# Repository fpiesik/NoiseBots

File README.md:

# NoiseBots
 A modular music making robot design

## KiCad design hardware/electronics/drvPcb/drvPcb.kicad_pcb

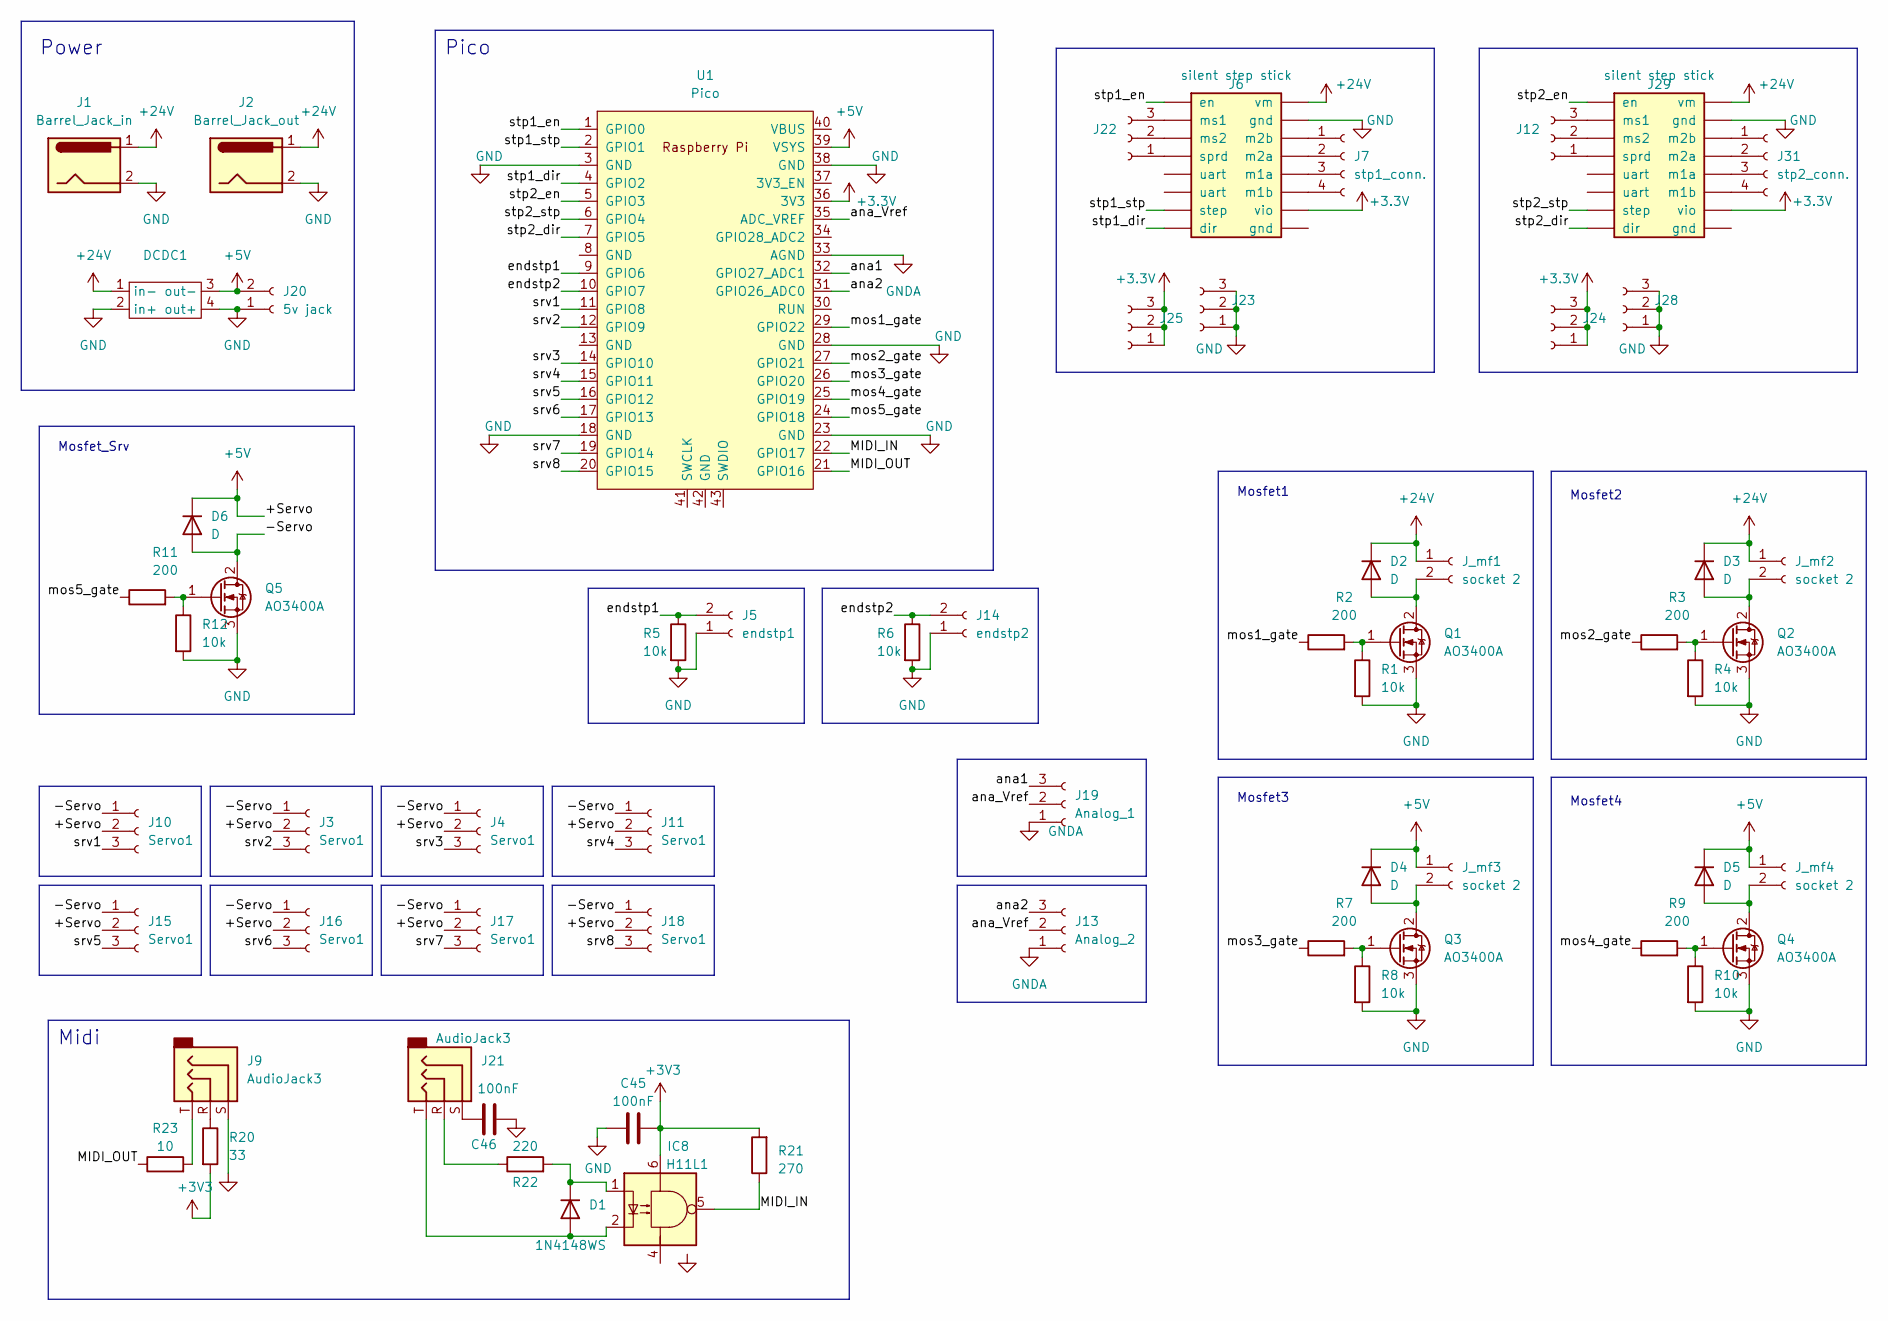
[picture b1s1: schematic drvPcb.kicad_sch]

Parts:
C45, C46: 100nF; C_1206_3216Metric_Pad1.33x1.80mm_HandSolder; LCSC C14663
D1: 1N4148WS; D_1206_3216Metric_Pad1.42x1.75mm_HandSolder; LCSC C2128
D2, D3, D4, D5, D6: D; D_1206_3216Metric_Pad1.42x1.75mm_HandSolder
DCDC1: Converter_DCDC
IC8: H11L1; SMDIP-6_W9.53mm; LCSC C78589
J1: Barrel_Jack_in; BarrelJack_GCT_DCJ200-10-A_Horizontal(fmod)
J2: Barrel_Jack_out; BarrelJack_GCT_DCJ200-10-A_Horizontal(fmod)
J3, J4, J10, J11, J15, J16, J17, J18: Servo1; PinHeader_1x03_P2.54mm_Vertical(fmod)
J5: endstp1; PinHeader_1x02_P2.54mm_Vertical_(fmod)
J6, J29: silent step stick; stepstick
J7: stp1_conn.; PinHeader_1x04_P2.54mm_Vertical(fmod)
J9, J21: AudioJack3; Jack_3.5mm_CUI_SJ1-3523N_Horizontal(fmod)
J12, J22, J23, J24, J25, J28: Conn_01x03_Socket; PinHeader_1x03_P2.54mm_Vertical(fmod)
J13: Analog_2; PinHeader_1x03_P2.54mm_Vertical(fmod)
J14: endstp2; PinHeader_1x02_P2.54mm_Vertical_(fmod)
J19: Analog_1; PinHeader_1x03_P2.54mm_Vertical(fmod)
J20: 5v jack; PinHeader_1x02_P2.54mm_Vertical_(fmod)
J31: stp2_conn.; PinHeader_1x04_P2.54mm_Vertical(fmod)
J_mf1, J_mf2, J_mf3, J_mf4: socket 2; PinHeader_1x02_P2.54mm_Vertical_(fmod)
Q1, Q2, Q3, Q4, Q5: AO3400A; SOT-223-3_TabPin2
R1, R4, R5, R6, R8, R10, R12: 10k; R_1206_3216Metric_Pad1.30x1.75mm_HandSolder
R2, R3, R7, R9, R11: 200; R_1206_3216Metric_Pad1.30x1.75mm_HandSolder
R20: 33; R_1206_3216Metric_Pad1.30x1.75mm_HandSolder; LCSC C23140
R21: 270; R_1206_3216Metric_Pad1.30x1.75mm_HandSolder; LCSC C22966
R22: 220; R_1206_3216Metric_Pad1.30x1.75mm_HandSolder; LCSC C25905
R23: 10; R_1206_3216Metric_Pad1.30x1.75mm_HandSolder; LCSC C22859
U1: Pico; RPi_Pico_SMD_TH

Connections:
+3.3V: J6.10 (vio), J24.1, J24.2, J24.3, J25.1, J25.2, J25.3, J29.10 (vio), U1.36 (3V3)
+3V3: C45.2, IC8.6, R20.2, R21.2
+5V: D4.1 (K), D5.1 (K), D6.1 (K), DCDC1.3 (out-), J3.2, J4.2, J10.2, J11.2, J15.2, J16.2, J17.2, J18.2, J20.2, J_mf3.1, J_mf4.1, U1.39 (VSYS)
+24V: D2.1 (K), D3.1 (K), DCDC1.1 (in-), J1.1, J2.1, J6.16 (vm), J29.16 (vm), J_mf1.1, J_mf2.1
/-Servo: D6.2 (A), J3.1, J4.1, J10.1, J11.1, J15.1, J16.1, J17.1, J18.1, Q5.2 (D)
/MIDI_IN: IC8.5, R21.1, U1.22 (GPIO17)
/MIDI_OUT: R23.1, U1.21 (GPIO16)
/ana1: J19.3, U1.32 (GPIO27_ADC1)
/ana2: J13.3, U1.31 (GPIO26_ADC0)
/ana_Vref: J13.2, J19.2, U1.35 (ADC_VREF)
/endstp1: J5.2, R5.1, U1.9 (GPIO6)
/endstp2: J14.2, R6.1, U1.10 (GPIO7)
/mos1_gate: R2.1, U1.29 (GPIO22)
/mos2_gate: R3.1, U1.27 (GPIO21)
/mos3_gate: R7.1, U1.26 (GPIO20)
/mos4_gate: R9.1, U1.25 (GPIO19)
/mos5_gate: R11.1, U1.24 (GPIO18)
/srv1: J10.3, U1.11 (GPIO8)
/srv2: J3.3, U1.12 (GPIO9)
/srv3: J4.3, U1.14 (GPIO10)
/srv4: J11.3, U1.15 (GPIO11)
/srv5: J15.3, U1.16 (GPIO12)
/srv6: J16.3, U1.17 (GPIO13)
/srv7: J17.3, U1.19 (GPIO14)
/srv8: J18.3, U1.20 (GPIO15)
/stp1_dir: J6.8 (dir), U1.4 (GPIO2)
/stp1_en: J6.1 (en), U1.1 (GPIO0)
/stp1_stp: J6.7 (step), U1.2 (GPIO1)
/stp2_dir: J29.8 (dir), U1.7 (GPIO5)
/stp2_en: J29.1 (en), U1.5 (GPIO3)
/stp2_stp: J29.7 (step), U1.6 (GPIO4)
GND: C45.1, C46.2, DCDC1.2 (in+), DCDC1.4 (out+), J1.2, J2.2, J5.1, J6.15 (gnd), J9.S, J14.1, J20.1, J23.1, J23.2, J23.3, J28.1, J28.2, J28.3, J29.15 (gnd), Q1.3 (S), Q2.3 (S), Q3.3 (S), Q4.3, Q5.3 (S), R1.2, R4.2, R5.2, R6.2, R8.2, R10.2, R12.2, U1.3 (GND), U1.18 (GND), U1.23 (GND), U1.28 (GND), U1.38 (GND)
GNDA: J13.1, J19.1, U1.33 (AGND)
unnamed: C46.1, J21.S
unnamed: D1.2 (A), IC8.2, J21.T
unnamed: D1.1 (K), IC8.1, R22.2
unnamed: D2.2 (A), J_mf1.2, Q1.2 (D)
unnamed: D3.2 (A), J_mf2.2, Q2.2 (D)
unnamed: D4.2 (A), J_mf3.2, Q3.2 (D)
unnamed: D5.2 (A), J_mf4.2, Q4.2
unnamed: J6.12 (m1a), J7.3
unnamed: J6.11 (m1b), J7.4
unnamed: J6.13 (m2a), J7.2
unnamed: J6.14 (m2b), J7.1
unnamed: J9.R, R20.1
unnamed: J9.T, R23.2
unnamed: J12.1, J29.4 (sprd)
unnamed: J12.2, J29.3 (ms2)
unnamed: J12.3, J29.2 (ms1)
unnamed: J21.R, R22.1
unnamed: J6.4 (sprd), J22.1
unnamed: J6.3 (ms2), J22.2
unnamed: J6.2 (ms1), J22.3
unnamed: J29.12 (m1a), J31.3
unnamed: J29.11 (m1b), J31.4
unnamed: J29.13 (m2a), J31.2
unnamed: J29.14 (m2b), J31.1
unnamed: Q1.1 (G), R1.1, R2.2
unnamed: Q2.1 (G), R3.2, R4.1
unnamed: Q3.1 (G), R7.2, R8.1
unnamed: Q4.1 (G), R9.2, R10.1
unnamed: Q5.1 (G), R11.2, R12.1

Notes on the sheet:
Midi
Mosfet3
Mosfet1
Mosfet2
Pico
Mosfet4
Power
Mosfet_Srv

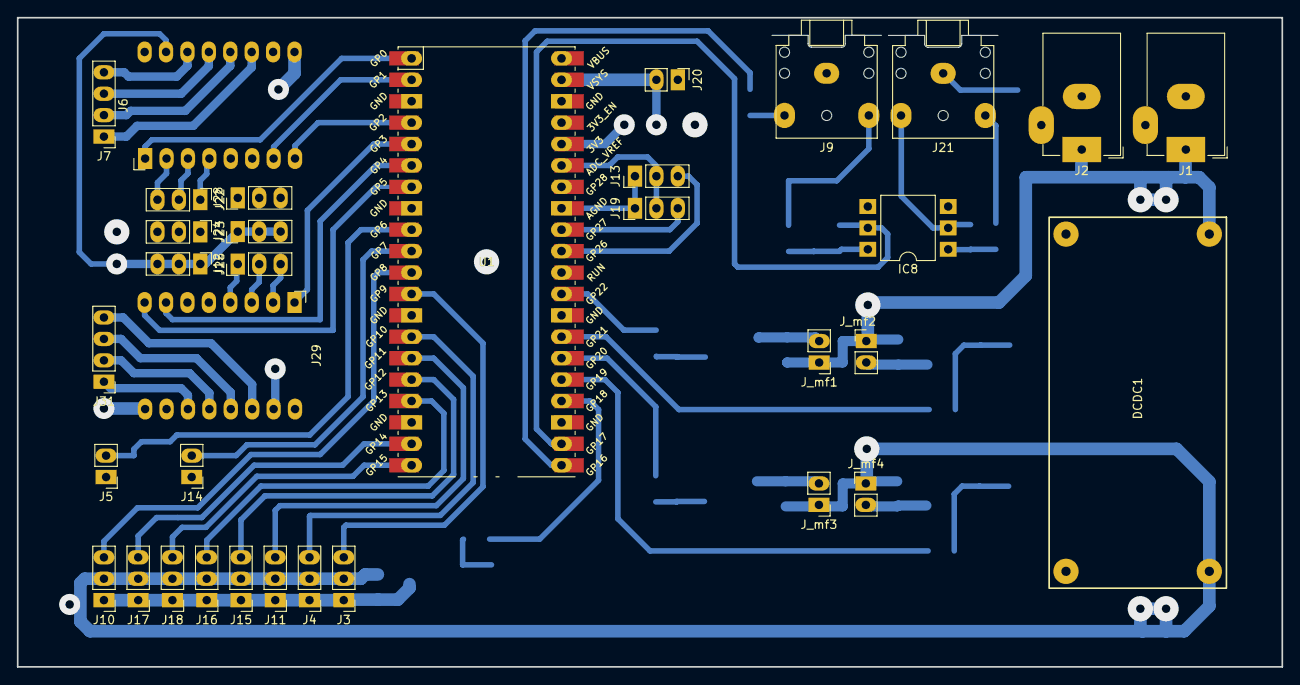
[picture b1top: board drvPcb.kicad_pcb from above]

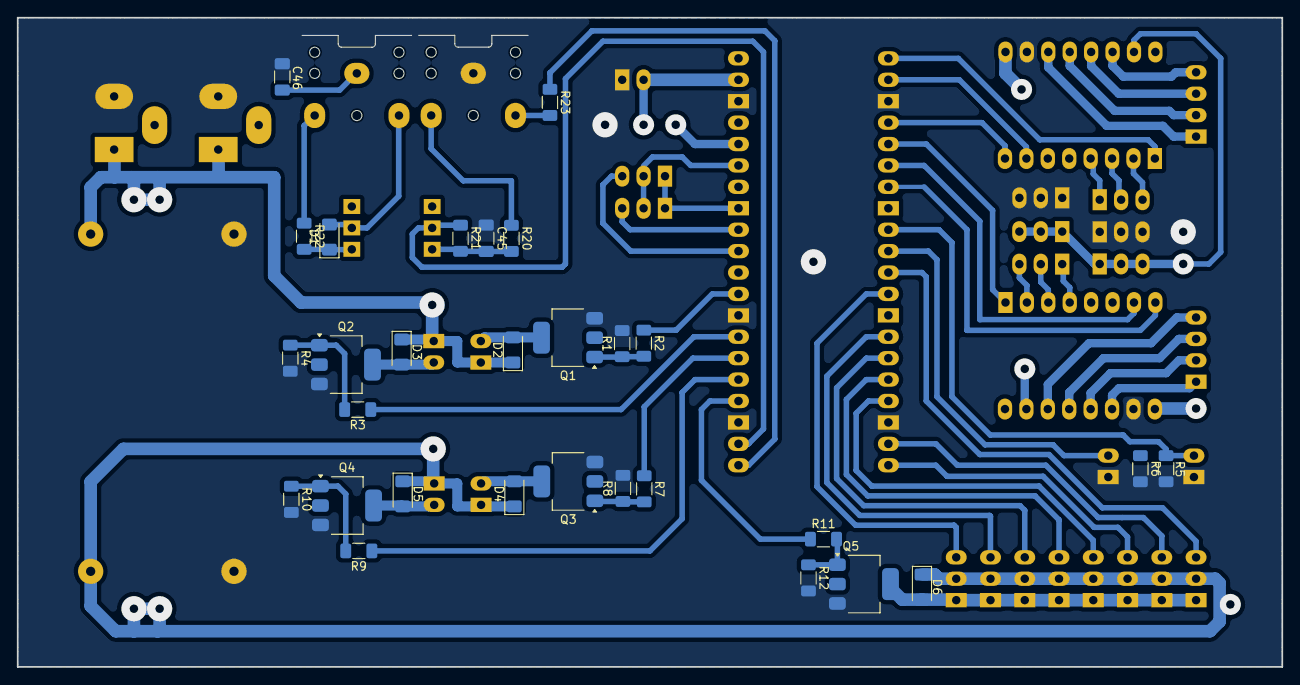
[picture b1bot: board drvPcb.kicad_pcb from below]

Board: 2 copper layers, 150.0 x 77.0 mm, 63 parts (29 on the bottom side), 62 nets.

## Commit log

2026-01-03 pcb enclosure
2026-01-09 pcb_mount
